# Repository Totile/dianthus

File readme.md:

# Dianthus

*In the world of GUI, less mouse pointers, more fat fingers buttons.* 

A button box to interface with web-based GUI, when you want to just push on buttons to do repetitive tasks. This replaces the need for the small buttons of a keyboard, or *worse*, a MOUSE.

* Hardware Supported: This box is based on the XB7 industrial button from Schneider electrics. And a promicro development board.
* Hardware Availability: 

## Installation guide

## Fabrication guide

All related documents can be found on the `livrables` folder (Procurement list, PCB production file, STL, ...)

### PCB Fabrication

### Schneider customisation button

### 3D printing files

The source files can be found on [Onshape project](https://cad.onshape.com/documents/cb52971ac28a8f36a2bdde5f/w/7d97d8c1100cd4f538ea172c/e/2ed6b61c8d6aeb3da16c9e53).

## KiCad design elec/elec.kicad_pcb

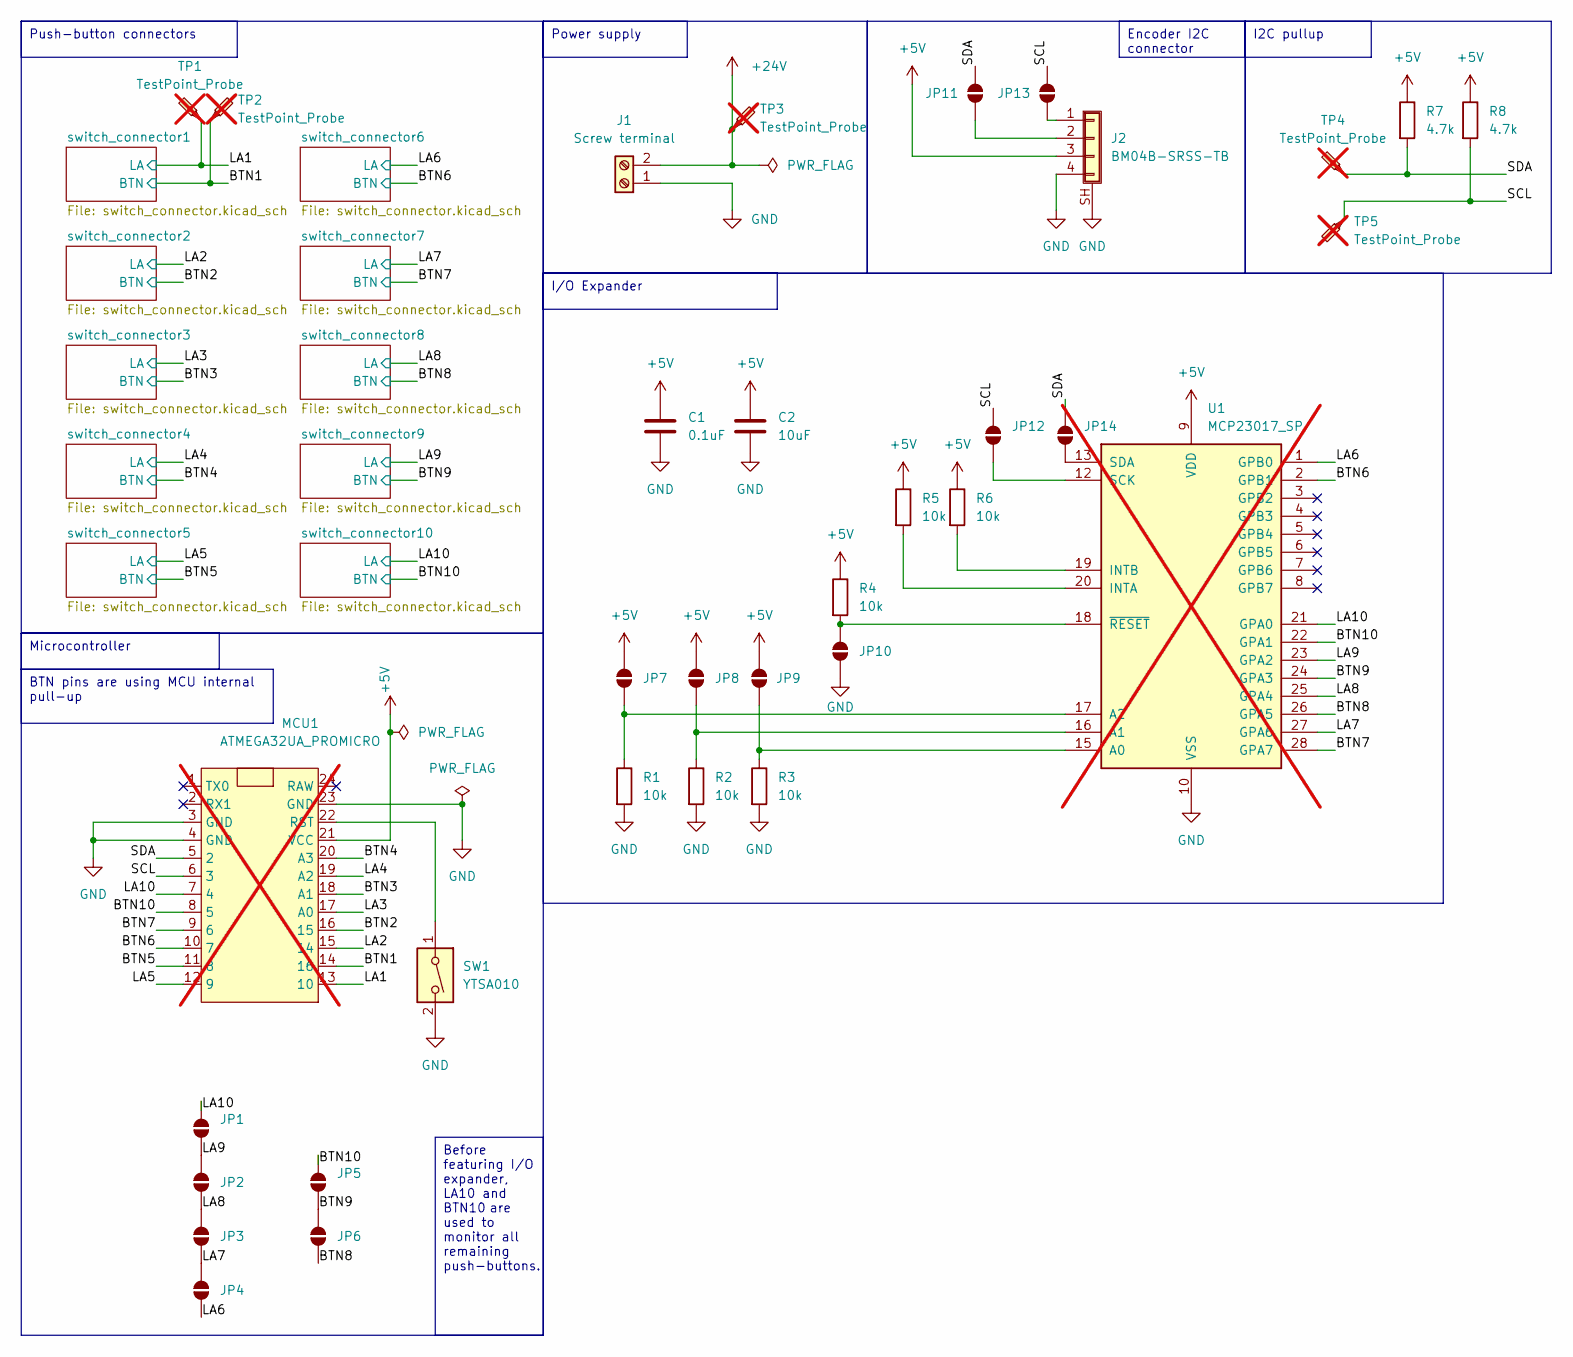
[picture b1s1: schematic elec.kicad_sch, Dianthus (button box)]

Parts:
C1: 0.1uF; C_0402_1005Metric; MPN C307331
C2: 10uF; C_1206_3216Metric; MPN C13585
J1: Screw terminal; DB301V-3.5-2P-GN-S; MPN C695629
J2: BM04B-SRSS-TB; JST_SH_BM04B-SRSS-TB_1x04-1MP_P1.00mm_Vertical; MPN C160390
JP1, JP2, JP3, JP4, JP5, JP6, JP7, JP8, JP9, JP10, JP11, JP12, JP13, JP14: SolderJumper_2_Open; SolderJumper-2_P1.3mm_Open_Pad1.0x1.5mm
MCU1: ATMEGA32UA_PROMICRO; ProMicro; not fitted
R1, R2, R3, R4, R5: 10k; R_0805_2012Metric; MPN C17414
R6: 10k; R_0805_2012Metric
R7, R8: 4.7k; R_0805_2012Metric; MPN C17675
SW1: YTSA010; YTS-C015-X; MPN C2910844
TP1, TP2, TP3, TP4, TP5: TestPoint_Probe; TestPoint_THTPad_D3.0mm_Drill1.5mm; not fitted
U1: MCP23017_SP; DIP-28_W7.62mm; not fitted

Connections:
+5V: C1.1, C2.1, J2.3, JP7.1 (A), JP8.1 (A), JP9.1 (A), MCU1.21 (VCC), R4.1, R5.1, R6.1, R7.1, R8.1, U1.9 (VDD)
+24V: J1.2, TP3.1; also elsewhere on the board
/BTN1: MCU1.14 (16), TP2.1; also elsewhere on the board
/BTN2: MCU1.16 (15); also elsewhere on the board
/BTN3: MCU1.18 (A1); also elsewhere on the board
/BTN4: MCU1.20 (A3); also elsewhere on the board
/BTN5: MCU1.11 (8); also elsewhere on the board
/BTN6: MCU1.10 (7), U1.2 (GPB1); also elsewhere on the board
/BTN7: MCU1.9 (6), U1.28 (GPA7); also elsewhere on the board
/BTN8: JP6.2 (B), U1.26 (GPA5); also elsewhere on the board
/BTN9: JP5.1 (A), JP6.1 (A), U1.24 (GPA3); also elsewhere on the board
/BTN10: JP5.2 (B), MCU1.8 (5), U1.22 (GPA1); also elsewhere on the board
/LA1: MCU1.13 (10), TP1.1; also elsewhere on the board
/LA2: MCU1.15 (14); also elsewhere on the board
/LA3: MCU1.17 (A0); also elsewhere on the board
/LA4: MCU1.19 (A2); also elsewhere on the board
/LA5: MCU1.12 (9); also elsewhere on the board
/LA6: JP4.1 (A), U1.1 (GPB0); also elsewhere on the board
/LA7: JP3.1 (A), JP4.2 (B), U1.27 (GPA6); also elsewhere on the board
/LA8: JP2.2 (B), JP3.2 (B), U1.25 (GPA4); also elsewhere on the board
/LA9: JP1.1 (A), JP2.1 (A), U1.23 (GPA2); also elsewhere on the board
/LA10: JP1.2 (B), MCU1.7 (4), U1.21 (GPA0); also elsewhere on the board
/SCL: JP12.2 (B), JP13.2 (B), MCU1.6 (3), R8.2, TP5.1
/SDA: JP11.2 (B), JP14.1 (A), MCU1.5 (2), R7.2, TP4.1
GND: C1.2, C2.2, J1.1, J2.4, J2.SH (Shield), JP10.1 (A), MCU1.3 (GND), MCU1.4 (GND), MCU1.23 (GND), R1.2, R2.2, R3.2, SW1.2, U1.10 (VSS); also elsewhere on the board
unnamed: J2.1, JP13.1 (A)
unnamed: J2.2, JP11.1 (A)
unnamed: JP7.2 (B), R1.1, U1.17 (A2)
unnamed: JP8.2 (B), R2.1, U1.16 (A1)
unnamed: JP9.2 (B), R3.1, U1.15 (A0)
unnamed: JP10.2 (B), R4.2, U1.18 (~RESET)
unnamed: JP12.1 (A), U1.12 (SCK)
unnamed: JP14.2 (B), U1.13 (SDA)
unnamed: MCU1.22 (RST), SW1.1
unnamed: R5.2, U1.20 (INTA)
unnamed: R6.2, U1.19 (INTB)

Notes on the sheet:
I2C pullup
Encoder I2C connector
BTN pins are using MCU internal pull-up
Push-button connectors
Before featuring I/O expander, LA10 and BTN10 are used to monitor all remaining push-buttons.
Power supply
I/O Expander
Microcontroller

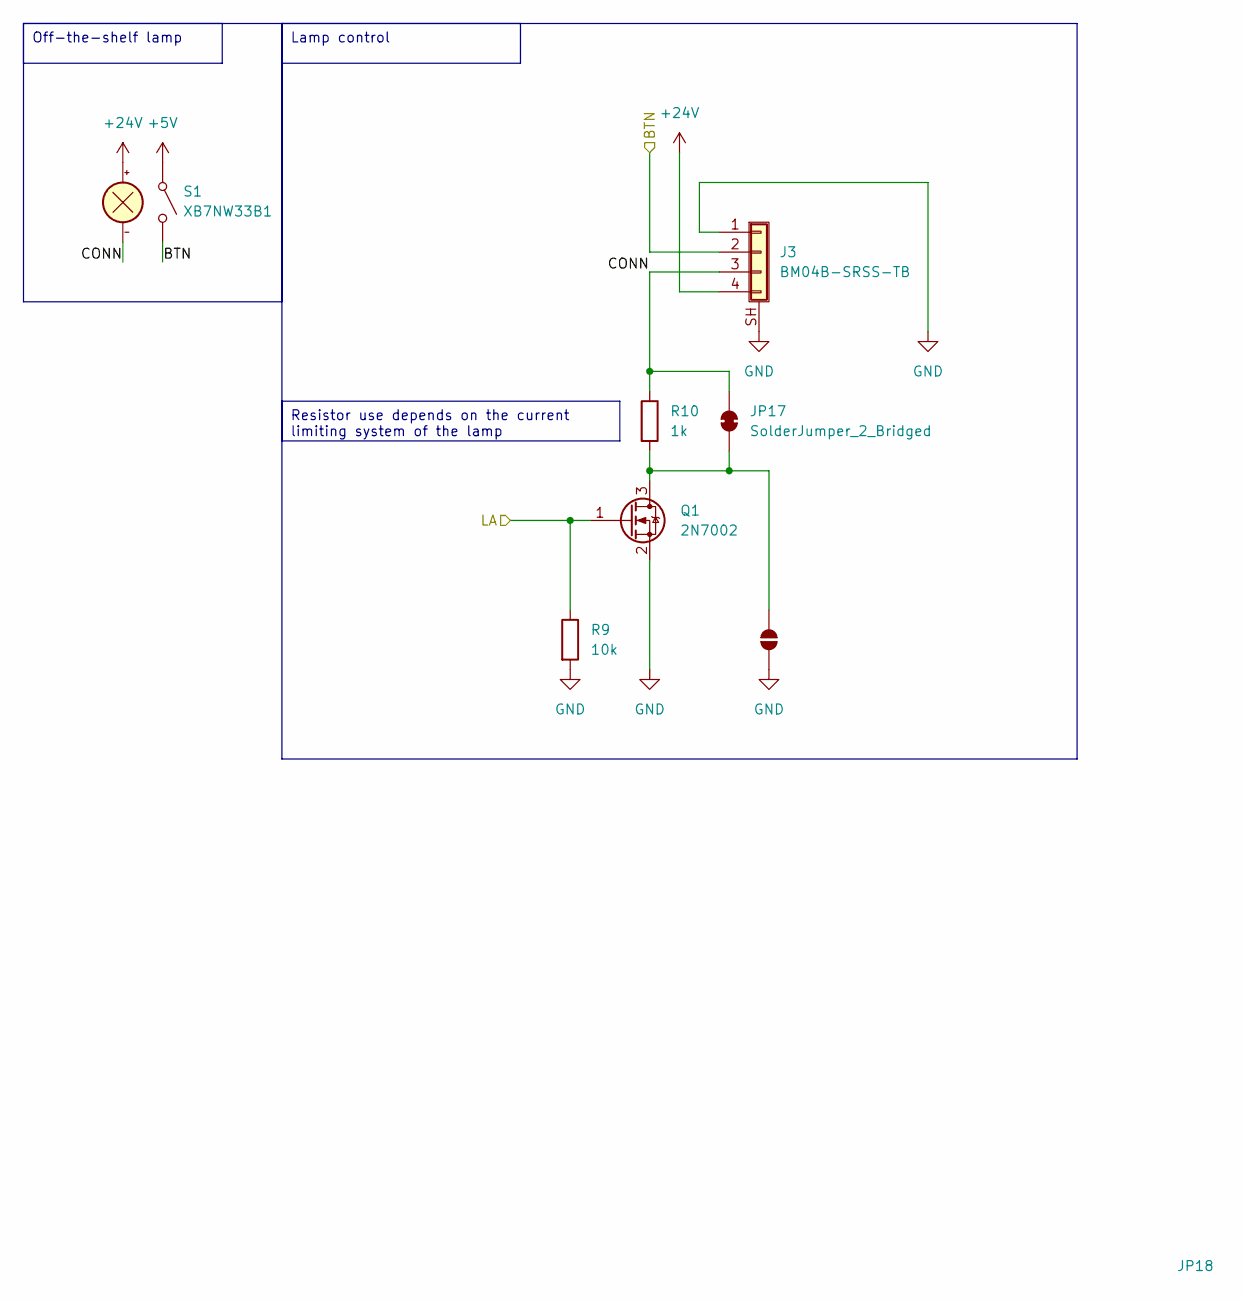
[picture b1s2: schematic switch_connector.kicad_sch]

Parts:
J3: BM04B-SRSS-TB; JST_SH_BM04B-SRSS-TB_1x04-1MP_P1.00mm_Vertical; MPN C160390
JP17: SolderJumper_2_Bridged; SolderJumper-2_P1.3mm_Bridged_Pad1.0x1.5mm
JP18: SolderJumper_2_Open; SolderJumper-2_P1.3mm_Open_Pad1.0x1.5mm
Q1: 2N7002; SOT-23; MPN C8545
R9: 10k; R_0805_2012Metric; MPN C17414
R10: 1k; R_0805_2012Metric; MPN C17513
S1: XB7NW33B1

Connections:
+24V: J3.4, S1.3 (x1(-)); also elsewhere on the board
/BTN1: J3.2; also elsewhere on the board
/LA1: Q1.1 (G), R9.1; also elsewhere on the board
GND: J3.1, J3.SH (Shield), JP18.2 (B), Q1.2 (S), R9.2; also elsewhere on the board

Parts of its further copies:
J4, J5, J6, J7, J8, J9, J10, J11, J12: BM04B-SRSS-TB; JST_SH_BM04B-SRSS-TB_1x04-1MP_P1.00mm_Vertical; MPN C160390
JP15, JP19, JP21, JP23, JP25, JP27, JP29, JP31, JP33: SolderJumper_2_Bridged; SolderJumper-2_P1.3mm_Bridged_Pad1.0x1.5mm
JP16, JP20, JP22, JP24, JP26, JP28, JP30, JP32, JP34: SolderJumper_2_Open; SolderJumper-2_P1.3mm_Open_Pad1.0x1.5mm
Q2, Q3, Q4, Q5, Q6, Q7, Q8, Q9, Q10: 2N7002; SOT-23; MPN C8545
R11, R13, R15, R17, R19, R21, R23, R25, R27: 10k; R_0805_2012Metric; MPN C17414
R12, R14, R16, R18, R20, R22, R24, R26, R28: 1k; R_0805_2012Metric; MPN C17513

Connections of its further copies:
+24V: J4.4, J5.4, J6.4, J7.4, J8.4, J9.4, J10.4, J11.4, J12.4; also elsewhere on the board
/BTN2: J4.2; also elsewhere on the board
/BTN3: J5.2; also elsewhere on the board
/BTN4: J6.2; also elsewhere on the board
/BTN5: J7.2; also elsewhere on the board
/BTN6: J8.2; also elsewhere on the board
/BTN7: J9.2; also elsewhere on the board
/BTN8: J10.2; also elsewhere on the board
/BTN9: J11.2; also elsewhere on the board
/BTN10: J12.2; also elsewhere on the board
/LA2: Q2.1 (G), R11.1; also elsewhere on the board
/LA3: Q3.1 (G), R13.1; also elsewhere on the board
/LA4: Q4.1 (G), R15.1; also elsewhere on the board
/LA5: Q5.1 (G), R17.1; also elsewhere on the board
/LA6: Q6.1 (G), R19.1; also elsewhere on the board
/LA7: Q7.1 (G), R21.1; also elsewhere on the board
/LA8: Q8.1 (G), R23.1; also elsewhere on the board
/LA9: Q9.1 (G), R25.1; also elsewhere on the board
/LA10: Q10.1 (G), R27.1; also elsewhere on the board
/switch_connector3/CONN: J5.3, JP19.2 (B), R14.1
/switch_connector4/CONN: J6.3, JP21.2 (B), R16.1
/switch_connector5/CONN: J7.3, JP23.2 (B), R18.1
/switch_connector6/CONN: J8.3, JP25.2 (B), R20.1
/switch_connector7/CONN: J9.3, JP27.2 (B), R22.1
/switch_connector8/CONN: J10.3, JP29.2 (B), R24.1
/switch_connector9/CONN: J11.3, JP31.2 (B), R26.1
/switch_connector10/CONN: J12.3, JP33.2 (B), R28.1
GND: J4.1, J4.SH (Shield), J5.1, J5.SH (Shield), J6.1, J6.SH (Shield), J7.1, J7.SH (Shield), J8.1, J8.SH (Shield), J9.1, J9.SH (Shield), J10.1, J10.SH (Shield), J11.1, J11.SH (Shield), J12.1, J12.SH (Shield), JP16.2 (B), JP20.2 (B), JP22.2 (B), JP24.2 (B), JP26.2 (B), JP28.2 (B), JP30.2 (B), JP32.2 (B), JP34.2 (B), Q2.2 (S), Q3.2 (S), Q4.2 (S), Q5.2 (S), Q6.2 (S), Q7.2 (S), Q8.2 (S), Q9.2 (S), Q10.2 (S), R11.2, R13.2, R15.2, R17.2, R19.2, R21.2, R23.2, R25.2, R27.2; also elsewhere on the board
unnamed: JP19.1 (A), JP20.1 (A), Q3.3 (D), R14.2
unnamed: JP21.1 (A), JP22.1 (A), Q4.3 (D), R16.2
unnamed: JP23.1 (A), JP24.1 (A), Q5.3 (D), R18.2
unnamed: JP25.1 (A), JP26.1 (A), Q6.3 (D), R20.2
unnamed: JP27.1 (A), JP28.1 (A), Q7.3 (D), R22.2
unnamed: JP29.1 (A), JP30.1 (A), Q8.3 (D), R24.2
unnamed: JP31.1 (A), JP32.1 (A), Q9.3 (D), R26.2
unnamed: JP33.1 (A), JP34.1 (A), Q10.3 (D), R28.2

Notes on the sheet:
Resistor use depends on the current limiting system of the lamp
Lamp control
Off-the-shelf lamp

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
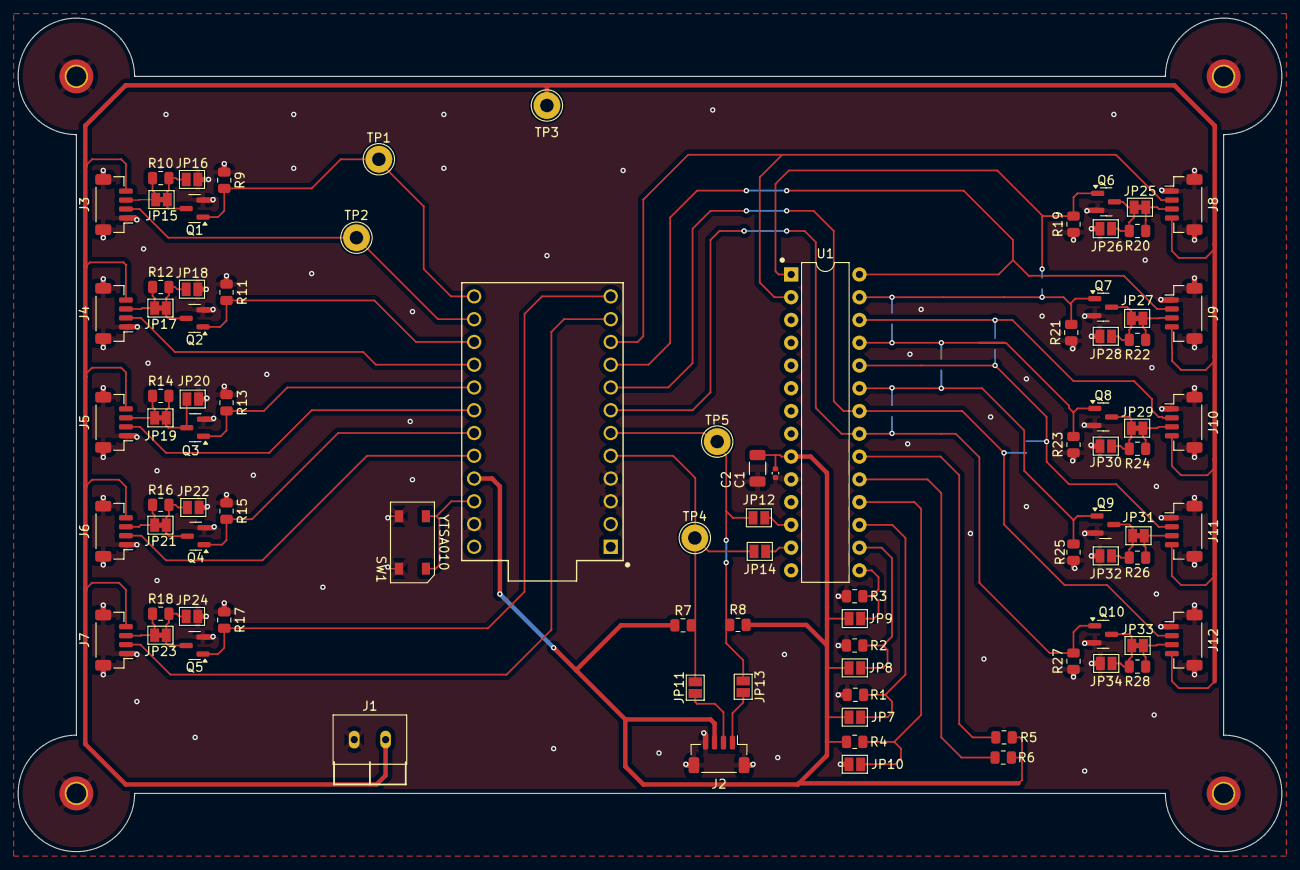
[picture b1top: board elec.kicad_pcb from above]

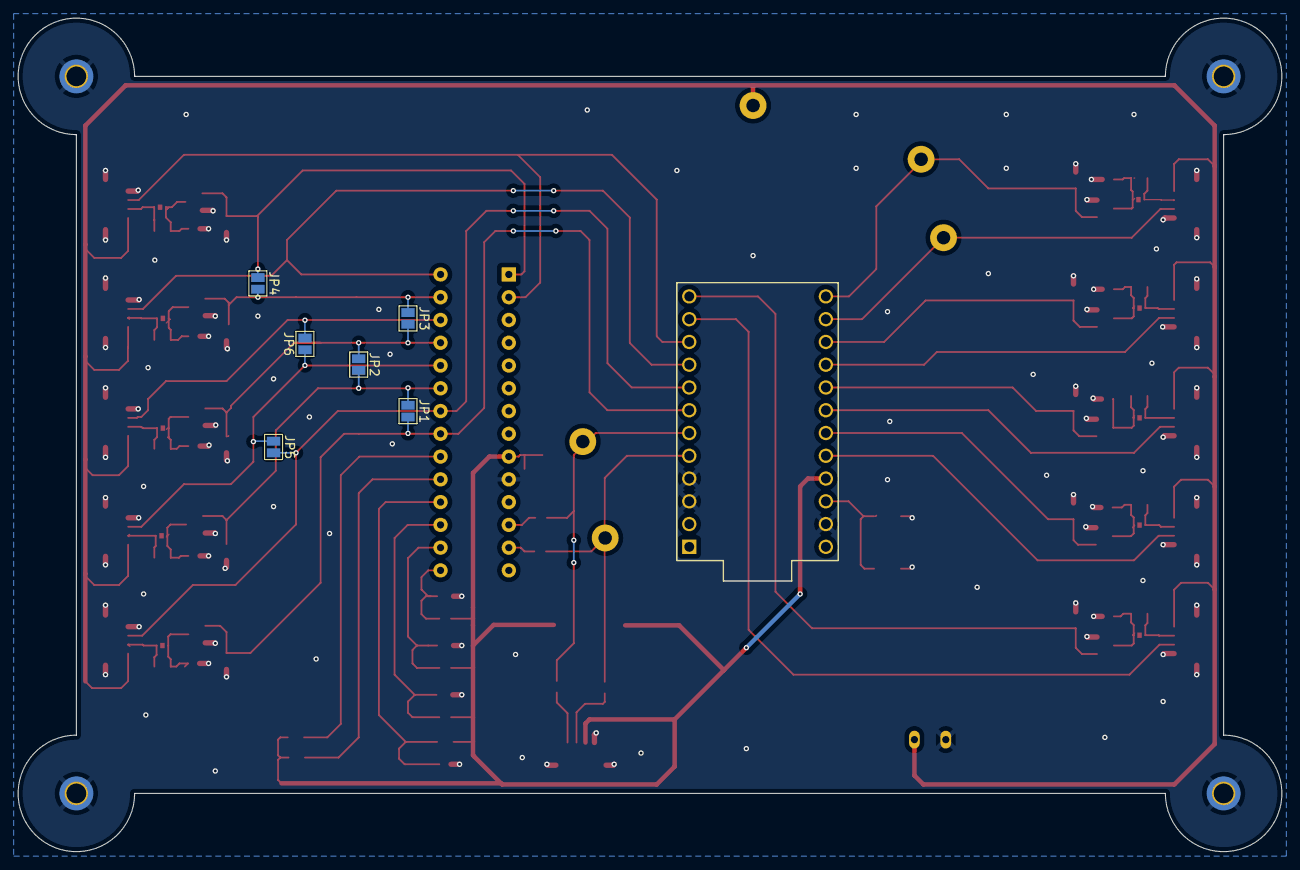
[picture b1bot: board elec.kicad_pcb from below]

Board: 2 copper layers, 141.0 x 93.0 mm, 94 parts (6 on the bottom side), 56 nets.

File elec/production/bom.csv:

Designator,Footprint,Quantity,Value,LCSC Part #
C1,0402,1,0.1uF,
C2,1206,1,10uF,
J1,DB301V-3.5-2P-GN-S,1,Screw terminal,
"J10, J11, J12, J2, J3, J4, J5, J6, J7, J8, J9",JST_SH_BM04B-SRSS-TB_1x04-1MP_P1.00mm_Vertical,11,BM04B-SRSS-TB,
MCU1,ProMicro,1,ATMEGA32UA_PROMICRO,
"Q1, Q10, Q2, Q3, Q4, Q5, Q6, Q7, Q8, Q9",SOT-23,10,2N7002,
"R1, R11, R13, R15, R17, R19, R2, R21, R23, R25, R27, R3, R4, R5, R6, R9",0805,16,10k,
"R10, R12, R14, R16, R18, R20, R22, R24, R26, R28",0805,10,1k,
"R7, R8",0805,2,4.7k,
SW1,YTS-C015-X,1,YTSA010,
"TP1, TP2, TP3, TP4, TP5",TestPoint_THTPad_D3.0mm_Drill1.5mm,5,TestPoint_Probe,
U1,DIP-28_W7.62mm,1,MCP23017_SP,

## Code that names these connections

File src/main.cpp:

#include "Arduino.h"
#include "Joystick.h"
#include "debounce.h"

// Pinout definition
const int PIN_LED1 = 3;
const int PIN_BTN1 = 15;
const int PIN_LED2 = 4;
const int PIN_BTN2 = 14;
const int PIN_LED3 = 5;
const int PIN_BTN3 = 16;

// Joystick initialisation
// TODO try to set it as a Gamepad, not a joystick
Joystick_ Joystick;

void buttonHandler(uint8_t btnID, uint8_t btnSTate) {
    if (btnSTate == BTN_PRESSED) {
        Joystick.pressButton(btnID);
        Serial.print("Button ");
        Serial.print(btnID);
        Serial.println(" pressed");
        digitalWrite(PIN_LED1, 1);
    } else {
        Joystick.releaseButton(btnID);
        Serial.print("Button ");
        Serial.print(btnID);
        Serial.println(" released");
        digitalWrite(PIN_LED1, 0);
    }
}

static Button btn1(0, buttonHandler);
static Button btn2(1, buttonHandler);
static Button btn3(2, buttonHandler);

void setup() {
    pinMode(PIN_BTN1, INPUT_PULLUP);
    pinMode(PIN_BTN2, INPUT_PULLUP);
    pinMode(PIN_BTN3, INPUT_PULLUP);
    pinMode(PIN_LED1, OUTPUT);

    Serial.begin(9600);
    Joystick.begin();
}

static void pollButtons() {
    btn1.update(digitalRead(PIN_BTN1));
    btn2.update(digitalRead(PIN_BTN2));
    btn3.update(digitalRead(PIN_BTN3));
}

void loop() {
    pollButtons();
    delay(10);
}

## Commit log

2024-03-13 update documentation
2024-03-24 chores: removing old project architecture
2024-03-24 chores: keep track of further reading documents
2024-03-24 chores: update new software architecture
2024-03-27 adding platformio support
2024-03-29 first draft with Joystick lib
2024-03-29 testing with debouncing lib
2024-03-29 3 button test with debounce
2024-04-19 first version without MOSFET
2024-04-24 feat: adding modularity to PCB
2024-04-24 adding datasheet
2024-04-24 moving images
2024-04-24 bugfix:debugging configuration
2024-04-24 feat: pretty serial print
2024-04-24 tracking deliverables
2024-04-24 feat: initialising vue
2024-04-24 chores: encapsulating controller code
2024-04-24 chore: .gitignore
2024-05-01 v1 3D print PCB
2024-05-04 PCB rev1, with production files
2024-05-04 doc: outline for fabrication guide
2024-05-12 stl preparation
2024-05-12 temp files for kicad
2024-05-12 doc: updating software
2024-05-12 chores: renaming vue project
2024-05-20 main - feat: updating delivrables
2024-05-20 dev - feat: 8 buttons with code repetition
2024-05-20 dev - refac: pin and lamp mode in for loop
2024-05-20 #1 - refac: further refactor of button loop definition
2024-05-20 #2 - bootstrap and first connection to gamepad
2024-05-20 2 - feat: polling gamepad status
2024-05-20 #2 - feat: making joystick dumber
2024-05-20 #1 - chores: removing legacy code
2024-05-20 #2 -refac: adding console logging
2024-05-20 #temp - mock commit to rollback previous version
2024-05-20 #2 - feat: making Joystick debounced again
2024-05-20 #2 - feat: debounced controller and working showroom
2024-05-20 feat: adding support for lamp debugging
2024-05-20 fixing and of merge
2024-05-20 dev: adding support for LED debugging
2024-05-26 feat - interfacing with Gamepad API - WIP encoder overshoot
2024-06-11 dev: adding encoder support with negative mod
2024-06-11 dev: updating pcb
2024-06-11 dev: adding export control documents
2024-06-11 dev: show encoder status in showroom
